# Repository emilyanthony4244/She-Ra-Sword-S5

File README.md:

# She-Ra Sword S5
 CAD, 3d Print Files, and Instructions for S5 SheRa sword

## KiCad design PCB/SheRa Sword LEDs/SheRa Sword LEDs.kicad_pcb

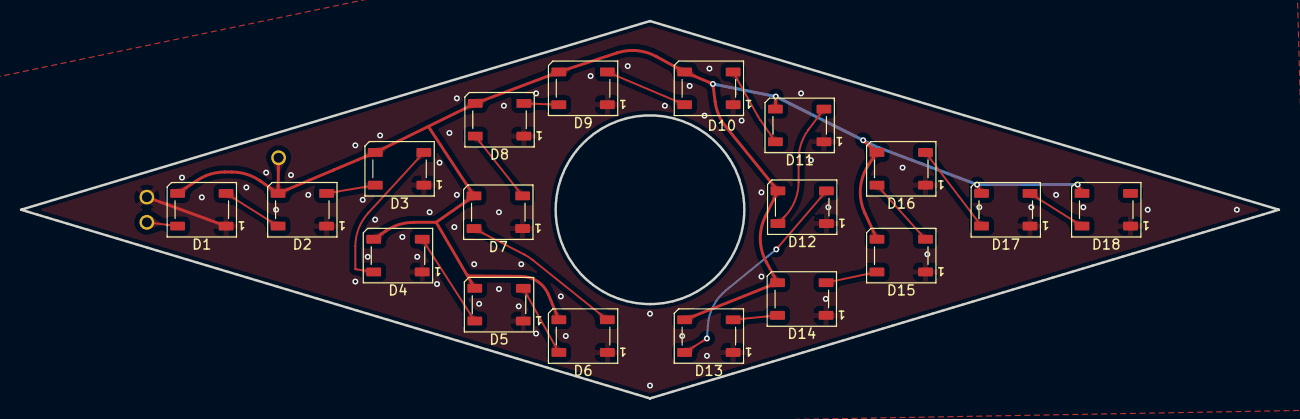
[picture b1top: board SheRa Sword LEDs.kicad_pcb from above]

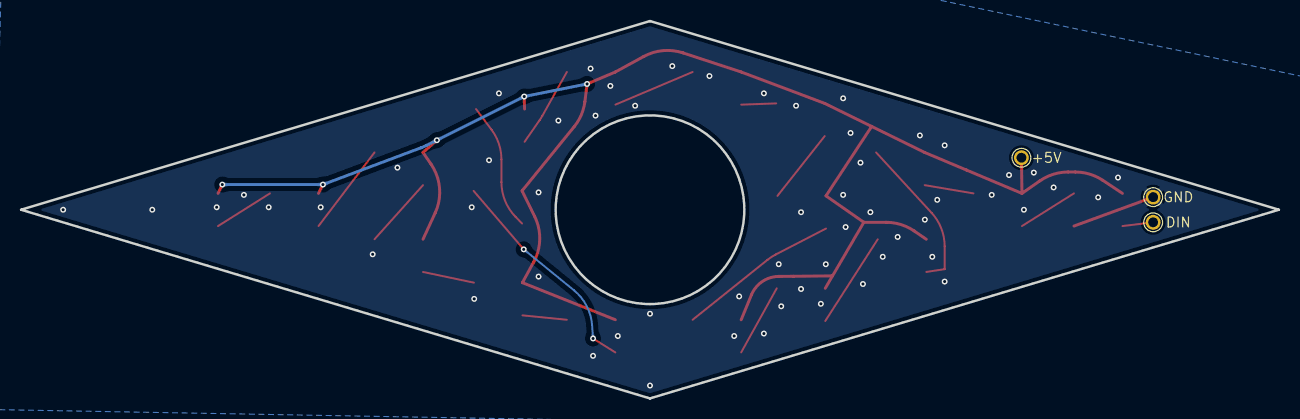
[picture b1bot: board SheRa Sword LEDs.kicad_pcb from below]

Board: 2 copper layers, 127.0 x 38.1 mm, 21 parts (3 on the bottom side), 19 nets.

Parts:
+5V: TestPoint_Pad_D1.5mm
D1, D2, D3, D4, D5, D6, D7, D8, D9, D10, D11, D12, D13, D14, D15, D16, D17, D18: WS2812B; LED_WS2812B_PLCC4_5.0x5.0mm_P3.2mm
DIN: TestPoint_Pad_D1.5mm
GND: TestPoint_Pad_D1.5mm

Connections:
GND: D1.1 (VDD), D2.1 (VDD), D3.1 (VDD), D4.1 (VDD), D5.1 (VDD), D6.1 (VDD), D7.1 (VDD), D8.1 (VDD), D9.1 (VDD), D10.1 (VDD), D11.1 (VDD), D12.1 (VDD), D13.1 (VDD), D14.1 (VDD), D15.1 (VDD), D16.1 (VDD), D17.1 (VDD), D18.1 (VDD), GND.1
unnamed: D1.2 (DOUT), D2.4 (DIN)
unnamed: +5V.1, D1.3 (VSS), D2.3 (VSS), D3.3 (VSS), D4.3 (VSS), D5.3 (VSS), D6.3 (VSS), D7.3 (VSS), D8.3 (VSS), D9.3 (VSS), D10.3 (VSS), D11.3 (VSS), D12.3 (VSS), D13.3 (VSS), D14.3 (VSS), D15.3 (VSS), D16.3 (VSS), D17.3 (VSS), D18.3 (VSS)
unnamed: D2.2 (DOUT), D3.4 (DIN)
unnamed: D3.2 (DOUT), D4.4 (DIN)
unnamed: D4.2 (DOUT), D5.4 (DIN)
unnamed: D5.2 (DOUT), D6.4 (DIN)
unnamed: D6.2 (DOUT), D7.4 (DIN)
unnamed: D7.2 (DOUT), D8.4 (DIN)
unnamed: D8.2 (DOUT), D9.4 (DIN)
unnamed: D9.2 (DOUT), D10.4 (DIN)
unnamed: D10.2 (DOUT), D11.4 (DIN)
unnamed: D11.2 (DOUT), D12.4 (DIN)
unnamed: D12.2 (DOUT), D13.4 (DIN)
unnamed: D13.2 (DOUT), D14.4 (DIN)
unnamed: D14.2 (DOUT), D15.4 (DIN)
unnamed: D15.2 (DOUT), D16.4 (DIN)
unnamed: D16.2 (DOUT), D17.4 (DIN)
unnamed: D17.2 (DOUT), D18.4 (DIN)

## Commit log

2023-08-12 pcb stuff
2025-08-12 Redesigning LED board and updating CAD
2025-08-12 STL Exports for printing
2025-08-13 cleanup files
    move 3dp files, delete old pcb data
